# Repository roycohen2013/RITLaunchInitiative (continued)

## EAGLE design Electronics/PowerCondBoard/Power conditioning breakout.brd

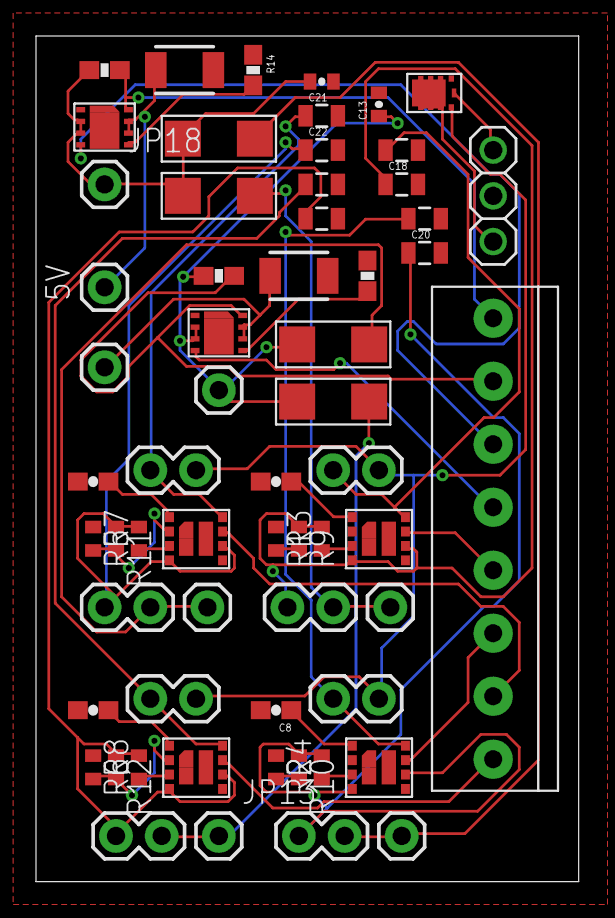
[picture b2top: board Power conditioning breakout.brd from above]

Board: 2 copper layers, 30.1 x 47.0 mm, 61 parts (0 on the bottom side), 43 nets.

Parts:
5V: M01PTH; 1X01
C3, C4: 150uF; 1210
C5, C6, C7, C8: 3.3nF; 0603-CAP
C9, C18, C19, C20, C21, C22, C23, C24: 22uF; 0805
C13, C14: .1uF; 0402-CAP
JP1: 1X08-3.5MM
JP2: 1X03
JP4, JP11, JP12, JP13, JP16, JP17, JP18: M01PTH; 1X01
JP19, JP20, JP21, JP22, JP23, JP24, JP25, JP26: M02PTH; 1X02
R1, R2, R5, R6: 180K; R0402
R3, R4, R7, R8: 10K; R0402
R9, R10: 1.02M; R0402
R11, R12: 634K; R0402
R13, R14: 20K; 0603-RES
R15, R16: 100K; 0603-RES
U$1: SI5410DU; CHIPFET
U$2, U$3, U$4, U$5: LMZ21701
U$6, U$7: TPS2556
U$8, U$9, U$10, U$11: MBRA210LT3; DO-214AC-SMA

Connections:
3.3V: C13.1, JP11.1, R15.2, U$7.P$2, U$7.P$3, U$8.P$1, U$9.P$1
+5V: C14.1, JP18.1, R16.2, U$6.P$2, U$6.P$3, U$10.P$1, U$11.P$1
EN1: JP2.3, U$1.P$6
EN31: JP1.1, U$5.P$7
EN32: JP1.2, U$4.P$7
EN51: JP1.3, U$3.P$7
EN52: JP1.4, U$2.P$7
ENT1: JP1.5, U$7.P$4
ENT2: JP1.6, U$6.P$4
F1: JP1.7, R15.1, U$7.P$8
F2: JP1.8, R16.1, U$6.P$8
GND: C3.1, C4.1, C5.2, C6.2, C7.2, C8.2, C9.2, C13.2, C14.2, C18.2, C19.2, C20.2, C21.2, C22.2, C23.2, C24.2, JP2.2, R1.1, R2.1, R5.1, R6.1, R13.1, R14.1, U$1.P$7, U$2.P$5, U$2.P$9, U$2.P$10, U$3.P$5, U$3.P$9, U$3.P$10, U$4.P$5, U$4.P$9, U$4.P$10, U$5.P$5, U$5.P$9, U$5.P$10, U$6.P$1, U$6.P$9, U$7.P$1, U$7.P$9
unnamed: C20.1, JP26.2, R4.2, R10.1, U$3.P$4, U$3.P$6
unnamed: R4.1, U$3.P$3
unnamed: R3.1, U$2.P$3
unnamed: R1.2, R9.2, U$2.P$2
unnamed: C4.2, JP4.1, U$7.P$6, U$7.P$7
unnamed: C7.1, U$2.P$1
unnamed: U$1.P$8, U$1.P$9, U$1.P$10
unnamed: R5.2, R11.2, U$4.P$2
unnamed: R2.2, R10.2, U$3.P$2
unnamed: JP12.1, JP22.2, U$9.P$2
unnamed: C8.1, U$3.P$1
unnamed: C5.1, U$4.P$1
unnamed: R7.1, U$4.P$3
unnamed: 5V.1, C3.2, U$6.P$6, U$6.P$7
unnamed: JP2.1, U$1.P$1, U$1.P$2, U$1.P$3, U$1.P$4
unnamed: R13.2, U$7.P$5
unnamed: R14.2, U$6.P$5
unnamed: C22.1, JP22.1, R7.2, R11.1, U$4.P$4, U$4.P$6
unnamed: C6.1, U$5.P$1
unnamed: C21.1, JP21.1, U$4.P$8
unnamed: C24.1, JP20.2, R8.2, R12.1, U$5.P$4, U$5.P$6
unnamed: R8.1, U$5.P$3
unnamed: R6.2, R12.2, U$5.P$2
unnamed: C23.1, JP19.1, U$5.P$8
unnamed: JP13.1, JP20.1, U$8.P$2
unnamed: JP16.1, JP24.1, U$10.P$2
unnamed: JP17.1, JP26.1, U$11.P$2
unnamed: C9.1, JP23.1, U$2.P$8
unnamed: C19.1, JP25.2, U$3.P$8
unnamed: C18.1, JP24.2, R3.2, R9.1, U$2.P$4, U$2.P$6
VIN: JP19.2, JP21.2, JP23.2, JP25.1, U$1.P$5

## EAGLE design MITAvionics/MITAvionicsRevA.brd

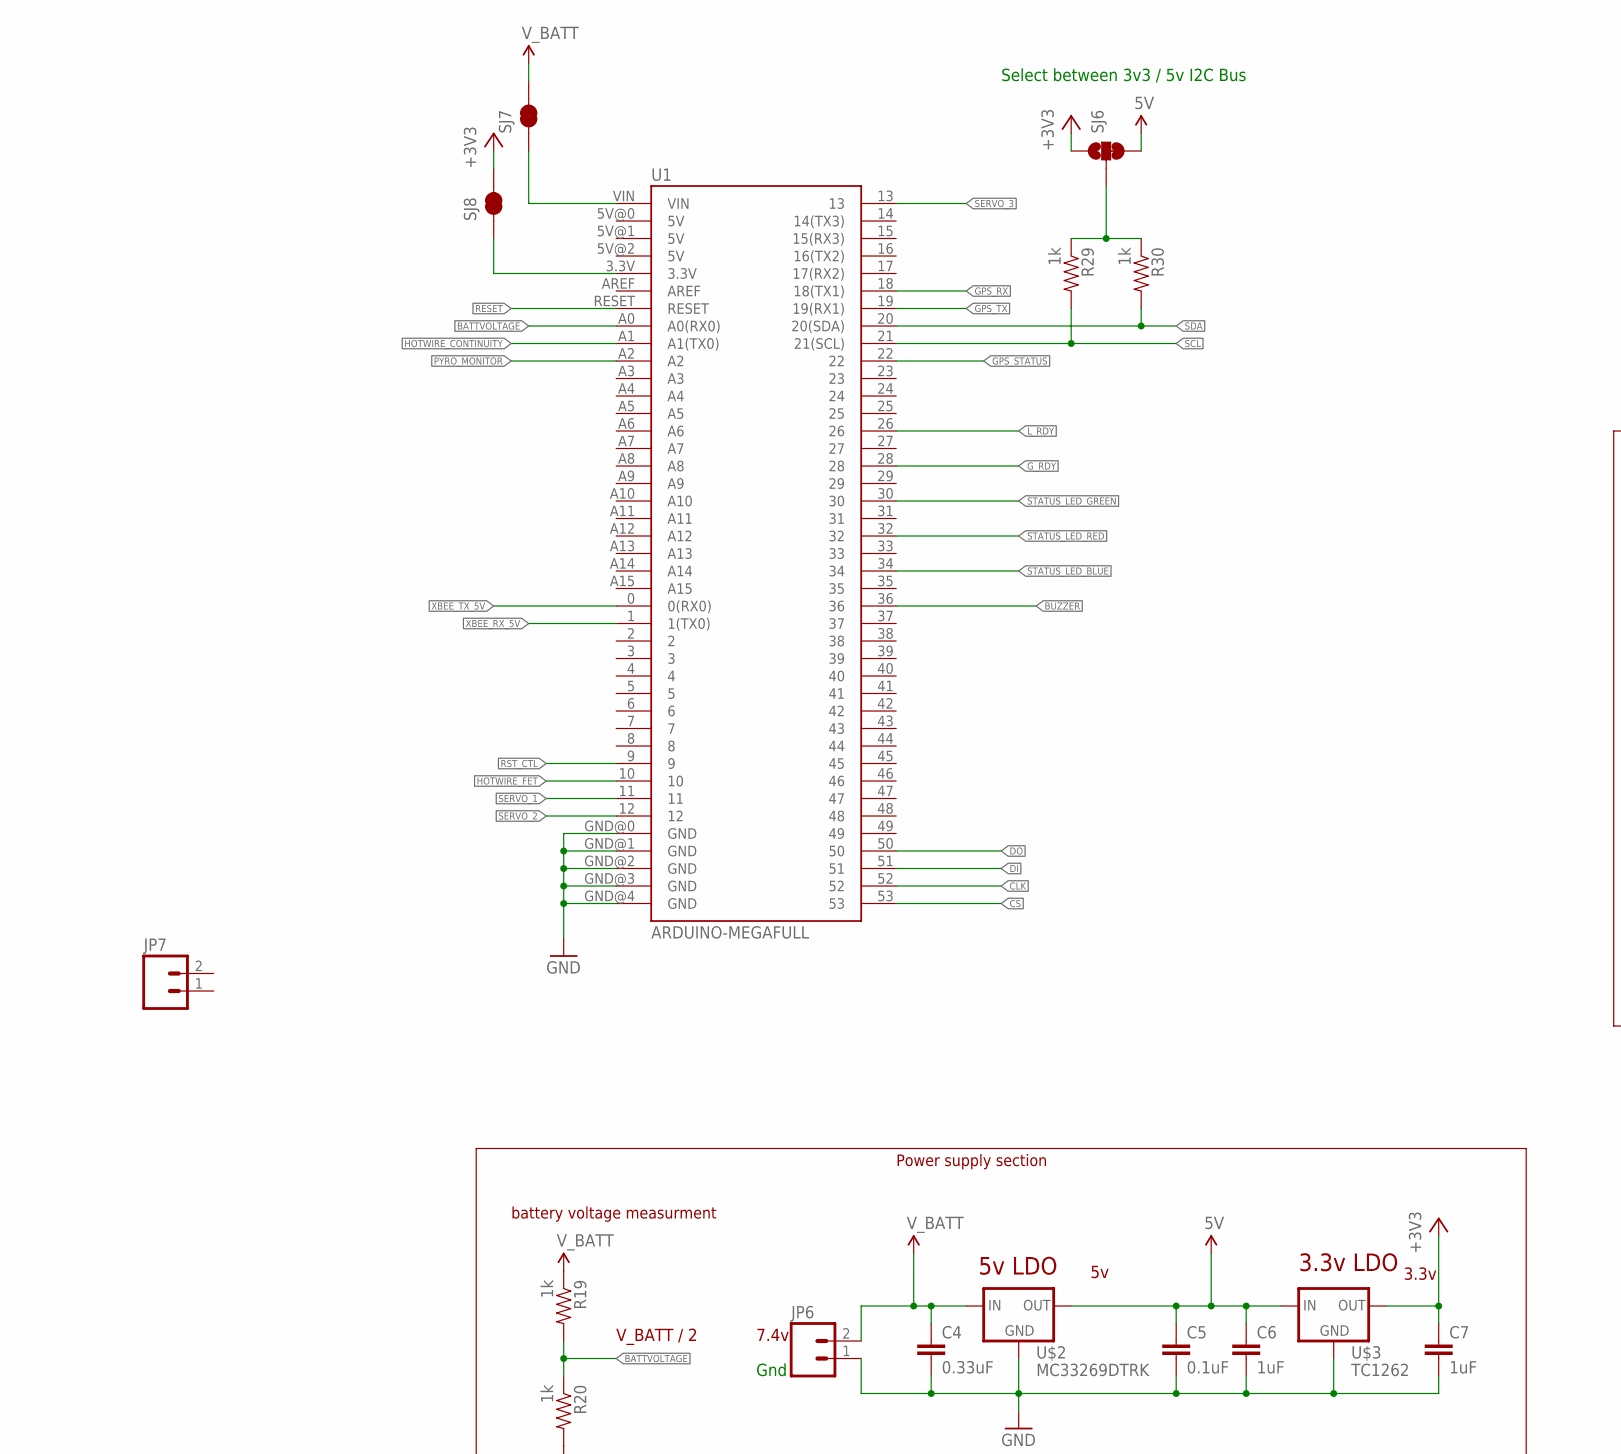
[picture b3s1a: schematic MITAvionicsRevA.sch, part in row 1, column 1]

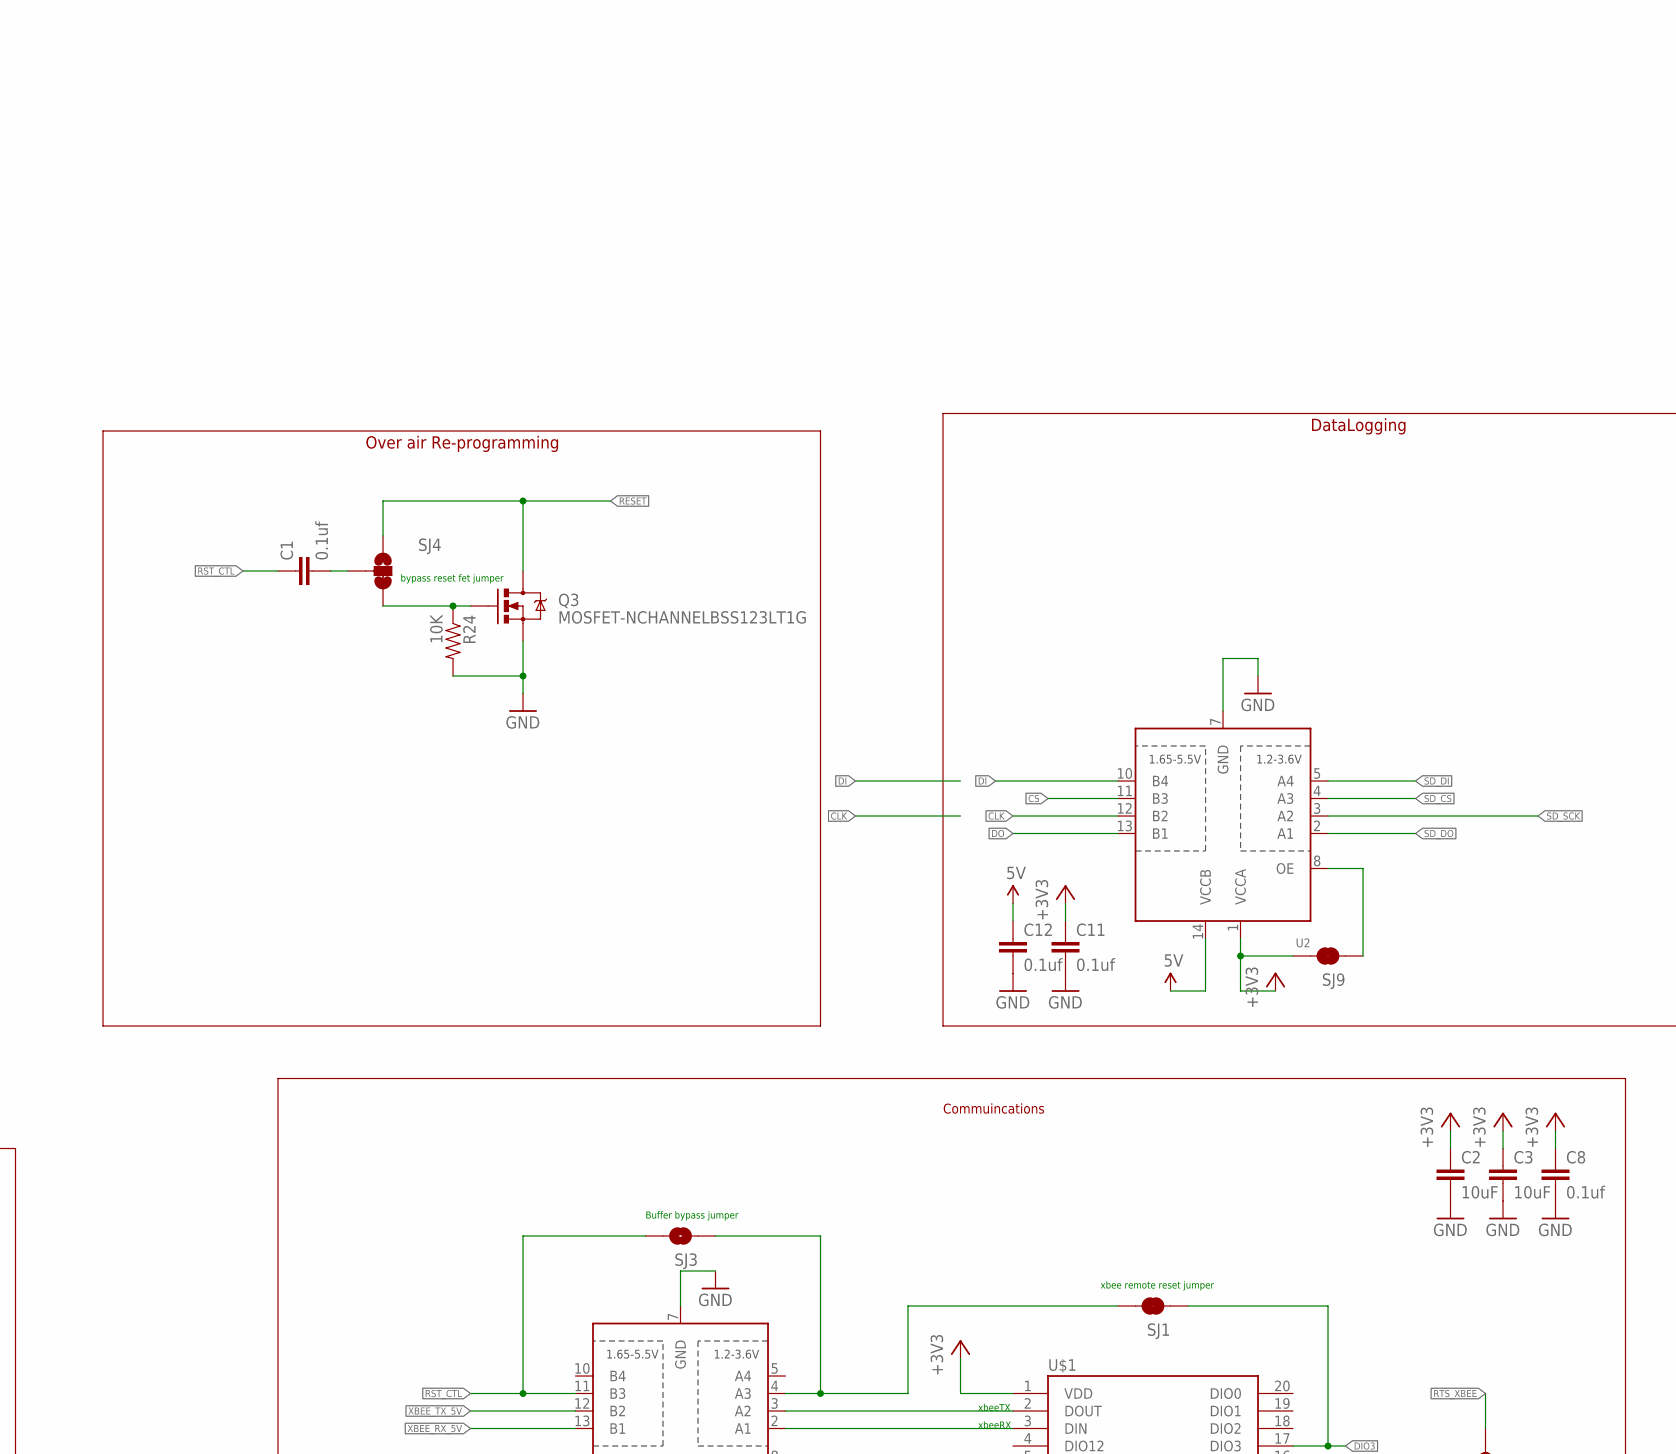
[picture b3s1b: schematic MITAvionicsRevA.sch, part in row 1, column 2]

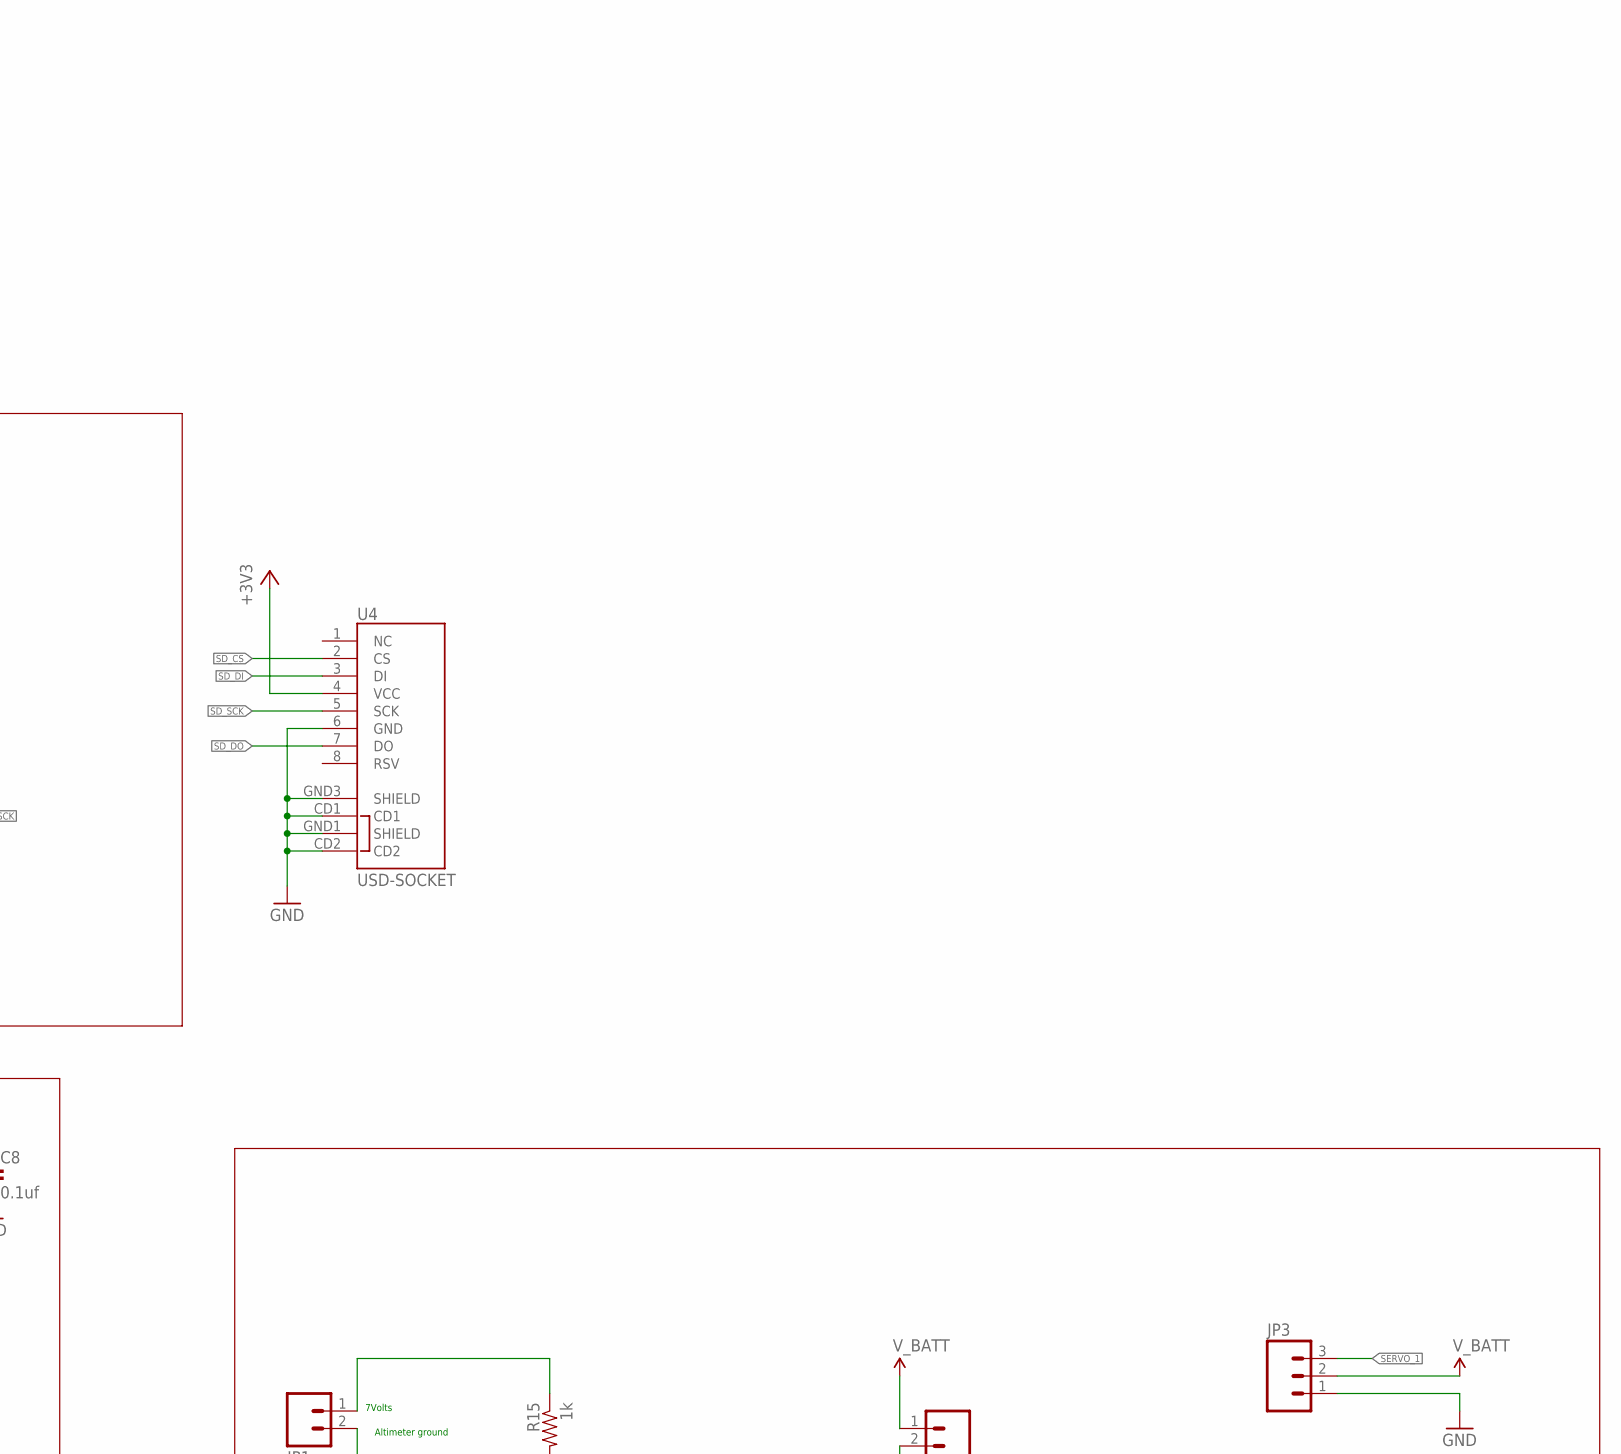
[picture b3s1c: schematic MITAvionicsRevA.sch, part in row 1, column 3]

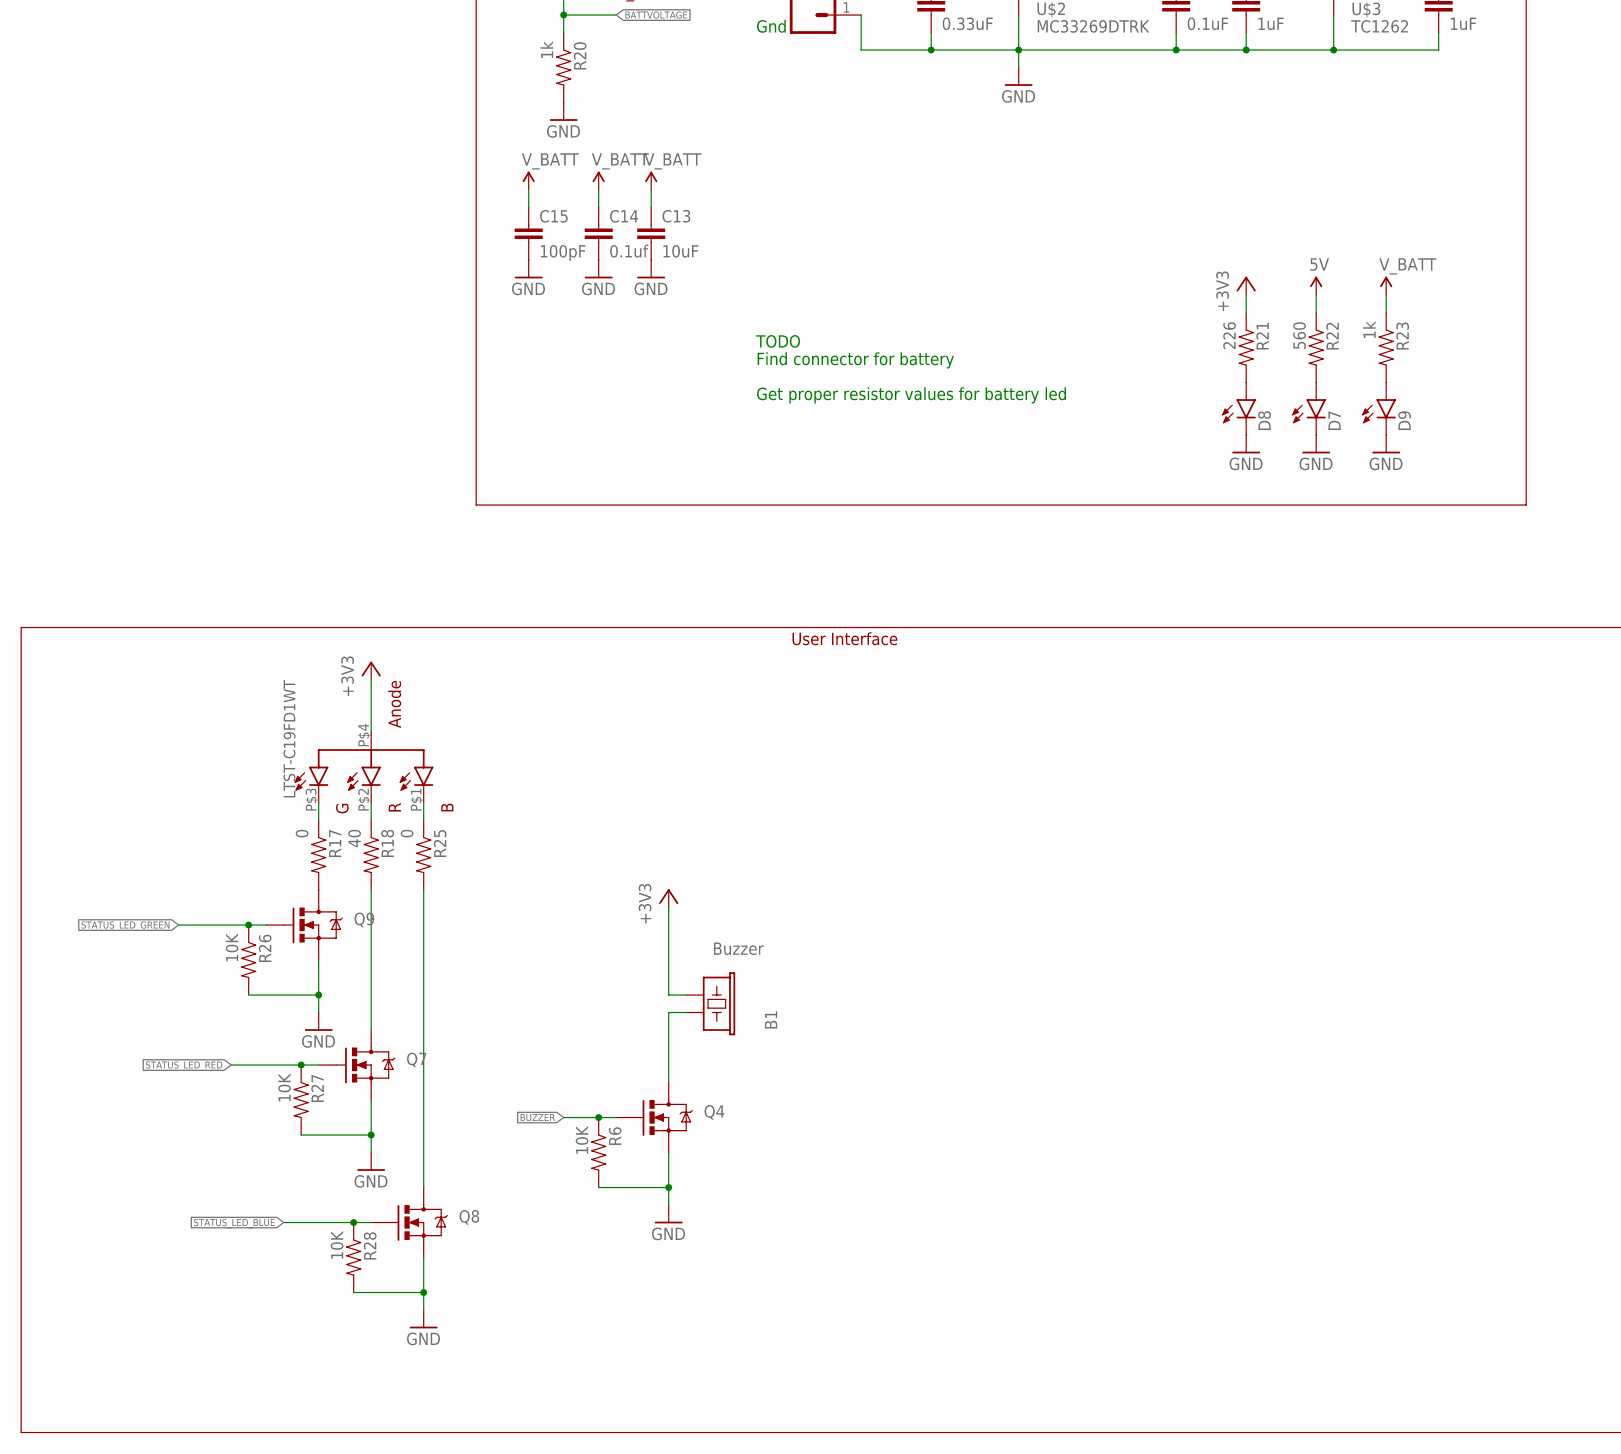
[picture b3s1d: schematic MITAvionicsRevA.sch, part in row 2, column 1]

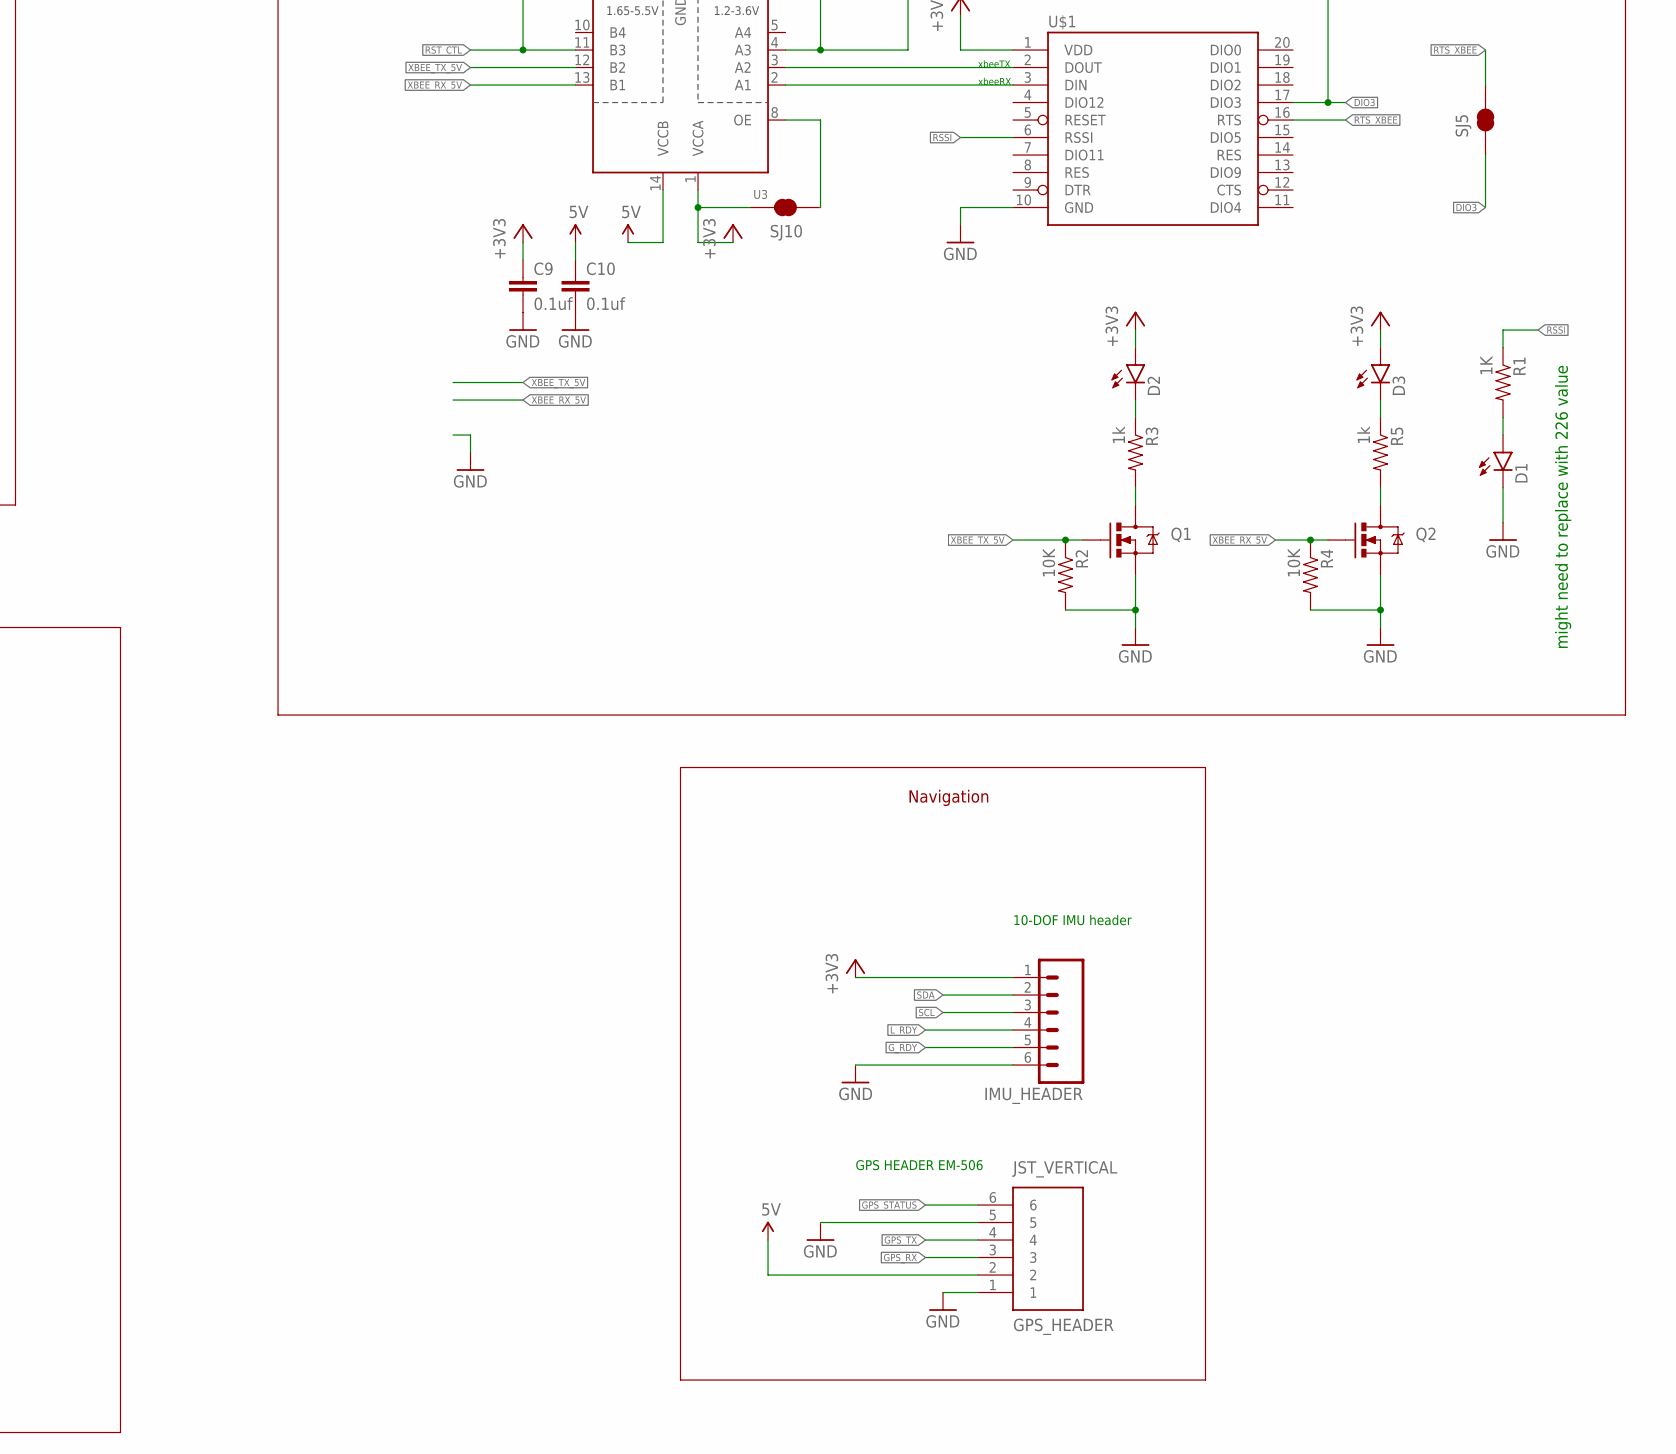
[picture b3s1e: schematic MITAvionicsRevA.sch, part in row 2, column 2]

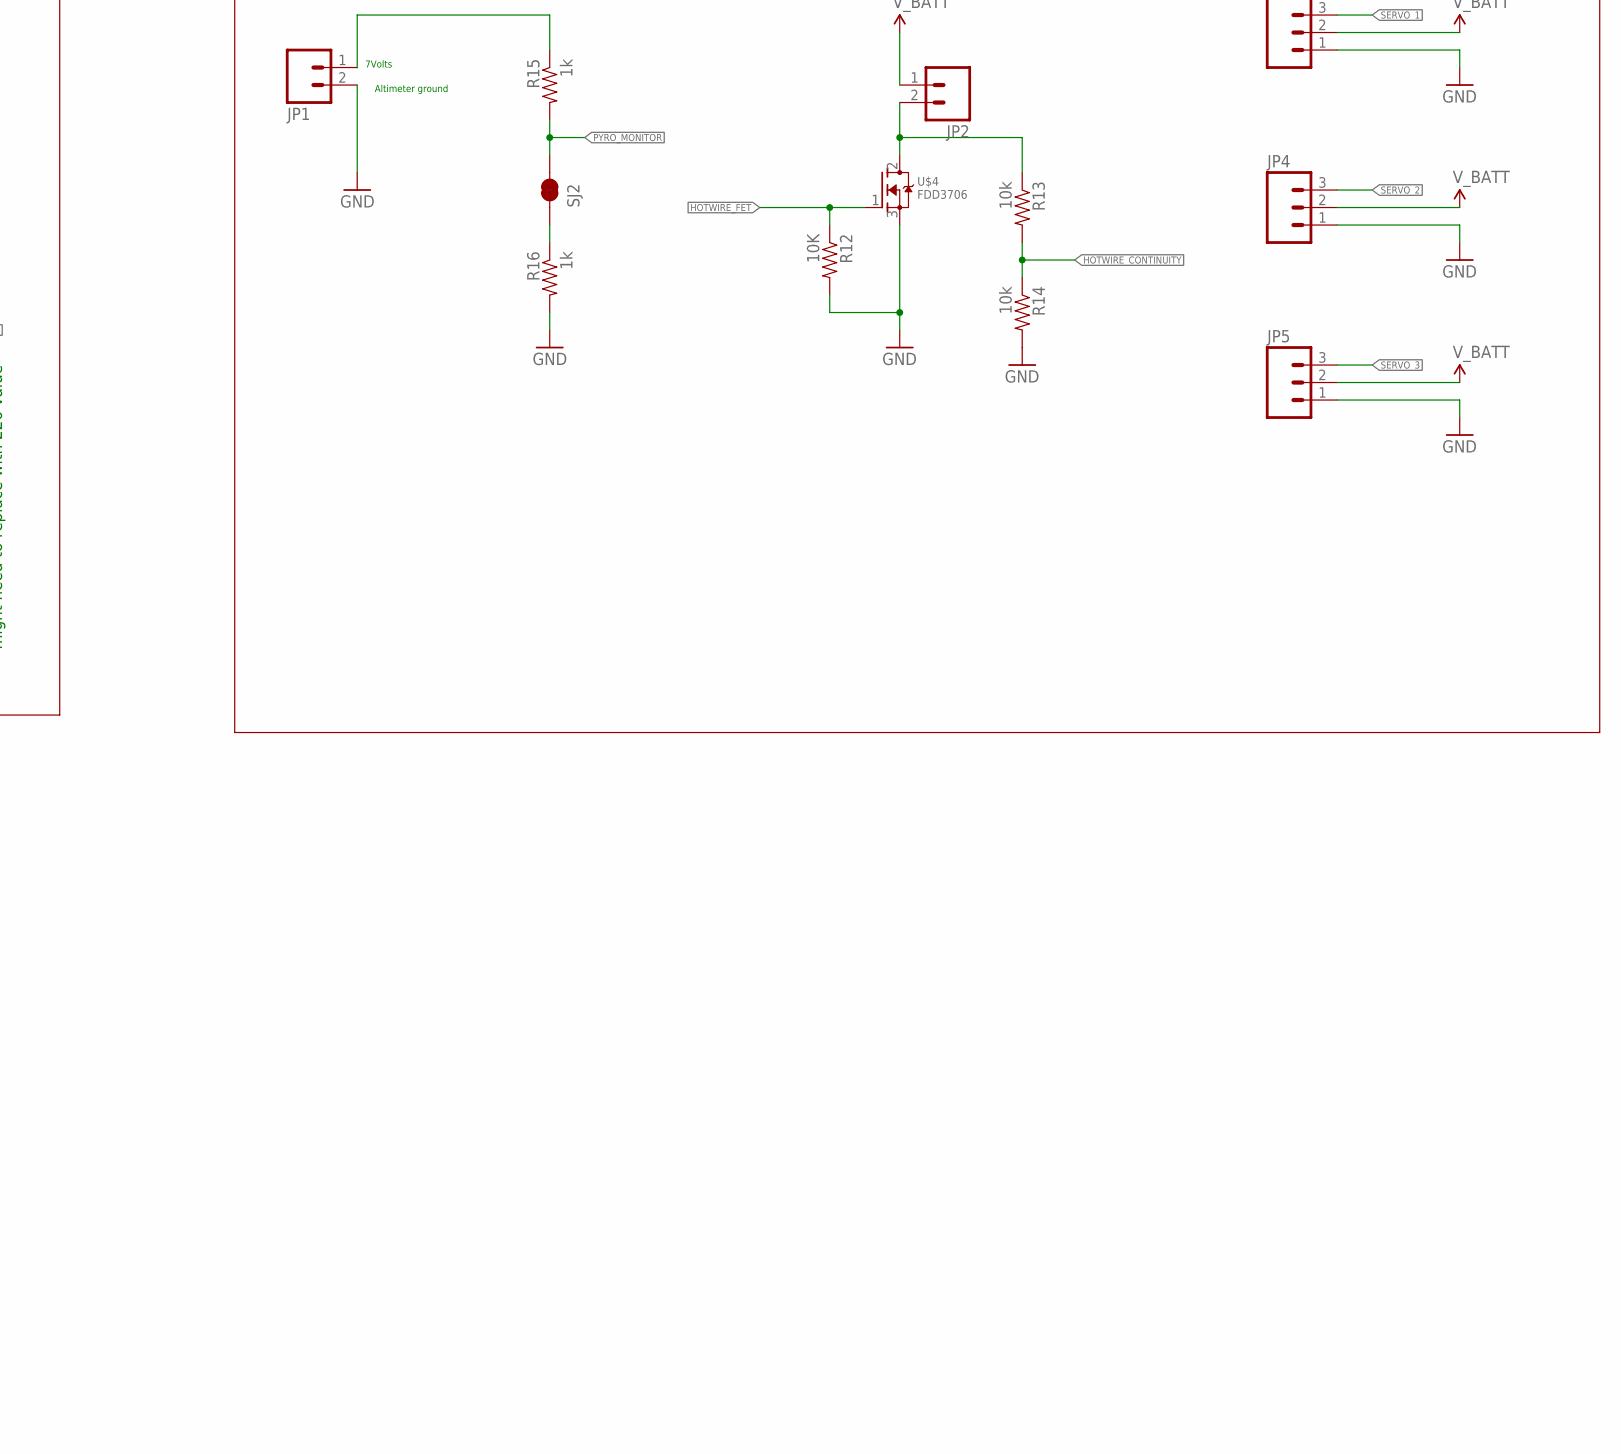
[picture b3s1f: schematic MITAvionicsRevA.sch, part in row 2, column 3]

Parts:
B1: Buzzer; BUZZER-CCV; DIGIKEY 102-1265-1-ND
C1, C8, C9, C10, C11, C12, C14: 0.1uf; 0805
C2, C3, C13: 10uF; 0805; DIGIKEY 490-3886-1-ND
C4: 0.33uF; 0805
C5: 0.1uF; 0805
C6, C7: 1uF; 0805
C15: 100pF; 0805
D1, D2, D3, D7, D8, D9: LED1206; LED-1206; DIGIKEY 160-1405-1-ND
GPS_HEADER: JST_VERTICAL; JST-6-SMD-VERT-1.0MM; DIGIKEY 455-1792-1-ND
IMU_HEADER: M06SMD-1MM; 1X06-1MM; DIGIKEY 455-1806-2-ND
JP1, JP2, JP6: M023.5MM; SCREWTERMINAL-3.5MM-2
JP3, JP4, JP5: M03PTH; 1X03
JP7: M02PTH; 1X02
Q1, Q2, Q3, Q4, Q7, Q8, Q9: MOSFET-NCHANNELBSS123LT1G; SOT23-3
R1: 1K; 0805
R2, R4, R6, R12, R24, R26, R27, R28: 10K; 0805
R3, R5, R15, R16, R19, R20, R29, R30: 1k; 0805
R13, R14: 10k; 0805
R17, R25: 0; 0805
R18: 40; 0805
R21: 226; 0805; DIGIKEY P226CCT-ND
R22: 560; 0805; DIGIKEY P560CCT-ND
R23: 1k; 0805; DIGIKEY P2.00KCCT-ND
SJ1, SJ2, SJ5, SJ7, SJ8, SJ9, SJ10: JUMPER-PAD-2-NC_BY_TRACE; PAD-JUMPER-2-NC_BY_TRACE_YES_SILK
SJ3: JUMPER-PAD-2-NOYES_SILK; PAD-JUMPER-2-NO_YES_SILK
SJ4, SJ6: JUMPER-PAD-3-2OF3_NC_BY_TRACE_SMALL; PAD-JUMPER-3-2OF3_NC_BY_TRACE_YES_SILK_FULL_BOX
U1: ARDUINO-MEGAFULL; ARDUINO_MEGA
U2, U3: TXB0104PWRSOIC14; SO14
U4: USD-SOCKET; MICROSD_1:1
U$1: XBEE-1B3; XBEE-SMD
U$2: MC33269DTRK; TO-252; DIGIKEY MC33269DTRK-5.0GOSCT-ND
U$3: TC1262; SOT223; DIGIKEY TC1262-3.3VDBCT-ND
U$4: FDD3706; TO-252
U$5: LTST-C19FD1WT; SMD-4

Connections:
5V: C5.1, C6.1, C10.1, C12.1, GPS_HEADER.2, R22.1, SJ6.3, U2.14 (VCCB), U3.14 (VCCB), U$2.2 (OUT), U$3.1 (IN)
+3V3: B1.- (2), C2.1, C3.1, C7.1, C8.1, C9.1, C11.1, D2.A, D3.A, IMU_HEADER.1, R21.1, SJ6.1, SJ8.2, SJ9.2, SJ10.2, U2.1 (VCCA), U3.1 (VCCA), U4.4 (VCC), U$1.1 (VDD), U$3.3 (OUT), U$5.P$4 (VCC)
BATTVOLTAGE: R19.2, R20.1, U1.A0 (A0(RX0))
BUZZER: Q4.1 (G), R6.1, U1.36
CLK: U1.52, U2.12 (B2)
CS: U1.53, U2.11 (B3)
DI: U1.51, U2.10 (B4)
DIO3: SJ1.1, SJ5.1, U$1.17 (DIO3)
DO: U1.50, U2.13 (B1)
GND: C2.2, C3.2, C4.2, C5.2, C6.2, C7.2, C8.2, C9.2, C10.2, C11.2, C12.2, C13.2, C14.2, C15.2, D1.C, D7.C, D8.C, D9.C, GPS_HEADER.1, GPS_HEADER.5, IMU_HEADER.6, JP1.2, JP3.1, JP4.1, JP5.1, JP6.1, Q1.2 (S), Q2.2 (S), Q3.2 (S), Q4.2 (S), Q7.2 (S), Q8.2 (S), Q9.2 (S), R2.2, R4.2, R6.2, R12.2, R14.2, R16.2, R20.2, R24.2, R26.2, R27.2, R28.2, U1.GND@0 (GND), U1.GND@1 (GND), U1.GND@2 (GND), U1.GND@3 (GND), U1.GND@4 (GND), U2.7 (GND), U3.7 (GND), U4.6 (GND), U4.CD1, U4.CD2, U4.GND1 (SHIELD), U4.GND3 (SHIELD), U$1.10 (GND), U$2.1 (GND), U$3.2 (GND), U$4.3 (S)
GPS_RX: GPS_HEADER.3, U1.18 (18(TX1))
GPS_STATUS: GPS_HEADER.6, U1.22
GPS_TX: GPS_HEADER.4, U1.19 (19(RX1))
G_RDY: IMU_HEADER.5, U1.28
HOTWIRE_CONTINUITY: R13.2, R14.1, U1.A1 (A1(TX0))
HOTWIRE_FET: R12.1, U1.10, U$4.1 (G)
L_RDY: IMU_HEADER.4, U1.26
unnamed: D1.A, R1.2
unnamed: SJ1.2, SJ3.1, U3.4 (A3)
unnamed: SJ8.1, U1.3.3V
unnamed: D3.C, R5.1
unnamed: JP2.2, R13.1, U$4.2 (D)
unnamed: Q3.1 (G), R24.1, SJ4.3
unnamed: C1.2, SJ4.2
unnamed: B1.+ (1), Q4.3 (D)
unnamed: Q2.3 (D), R5.2
unnamed: D2.C, R3.1
unnamed: Q1.3 (D), R3.2
unnamed: SJ9.1, U2.8 (OE)
unnamed: SJ10.1, U3.8 (OE)
unnamed: Q9.3 (D), R17.2
unnamed: Q7.3 (D), R18.2
unnamed: D7.A, R22.2
unnamed: D8.A, R21.2
unnamed: D9.A, R23.2
unnamed: Q8.3 (D), R25.2
unnamed: JP1.1, R15.1
unnamed: R29.1, R30.1, SJ6.2
unnamed: SJ7.1, U1.VIN
unnamed: R16.1, SJ2.1
unnamed: R17.1, U$5.P$3 (GREEN)
unnamed: R18.1, U$5.P$2 (RED)
unnamed: R25.1, U$5.P$1 (BLUE)
PYRO_MONITOR: R15.2, SJ2.2, U1.A2
RESET: Q3.3 (D), SJ4.1, U1.RESET
RSSI: R1.1, U$1.6 (RSSI)
RST_CTL: C1.1, SJ3.2, U1.9, U3.11 (B3)
RTS_XBEE: SJ5.2, U$1.16 (RTS)
SCL: IMU_HEADER.3, R29.2, U1.21 (21(SCL))
SDA: IMU_HEADER.2, R30.2, U1.20 (20(SDA))
SD_CS: U2.4 (A3), U4.2 (CS)
SD_DI: U2.5 (A4), U4.3 (DI)
SD_DO: U2.2 (A1), U4.7 (DO)
SD_SCK: U2.3 (A2), U4.5 (SCK)
SERVO_1: JP3.3, U1.11
SERVO_2: JP4.3, U1.12
SERVO_3: JP5.3, U1.13
STATUS_LED_BLUE: Q8.1 (G), R28.1, U1.34
STATUS_LED_GREEN: Q9.1 (G), R26.1, U1.30
STATUS_LED_RED: Q7.1 (G), R27.1, U1.32
V_BATT: C4.1, C13.1, C14.1, C15.1, JP2.1, JP3.2, JP4.2, JP5.2, JP6.2, R19.1, R23.1, SJ7.2, U$2.3 (IN)
XBEE_RX_3V3: U3.2 (A1), U$1.3 (DIN)
XBEE_RX_5V: Q2.1 (G), R4.1, U1.1 (1(TX0)), U3.13 (B1)
XBEE_TX_3V3: U3.3 (A2), U$1.2 (DOUT)
XBEE_TX_5V: Q1.1 (G), R2.1, U1.0 (0(RX0)), U3.12 (B2)

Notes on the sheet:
Gnd
5v LDO
3.3v LDO
battery voltage measurment
Power supply section
TODO
Find connector for battery
Get proper resistor values for battery led
xbeeTX
xbeeRX
Buffer bypass jumper
xbee remote reset jumper
bypass reset fet jumper
Commuincations
7.4v
V_BATT / 2
User Interface
7Volts
Altimeter ground
Select between 3v3 / 5v I2C Bus
10-DOF IMU header
GPS HEADER EM-506
Over air Re-programming
DataLogging
Navigation
might need to replace with 226 value

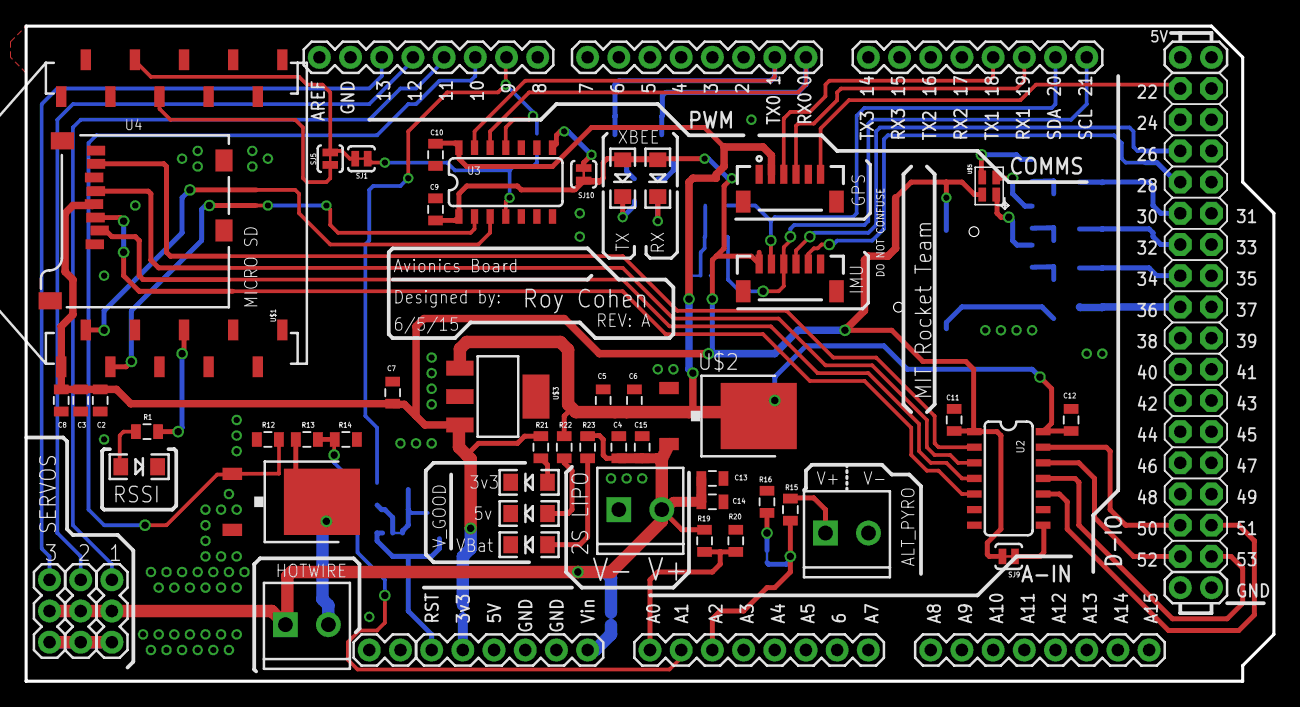
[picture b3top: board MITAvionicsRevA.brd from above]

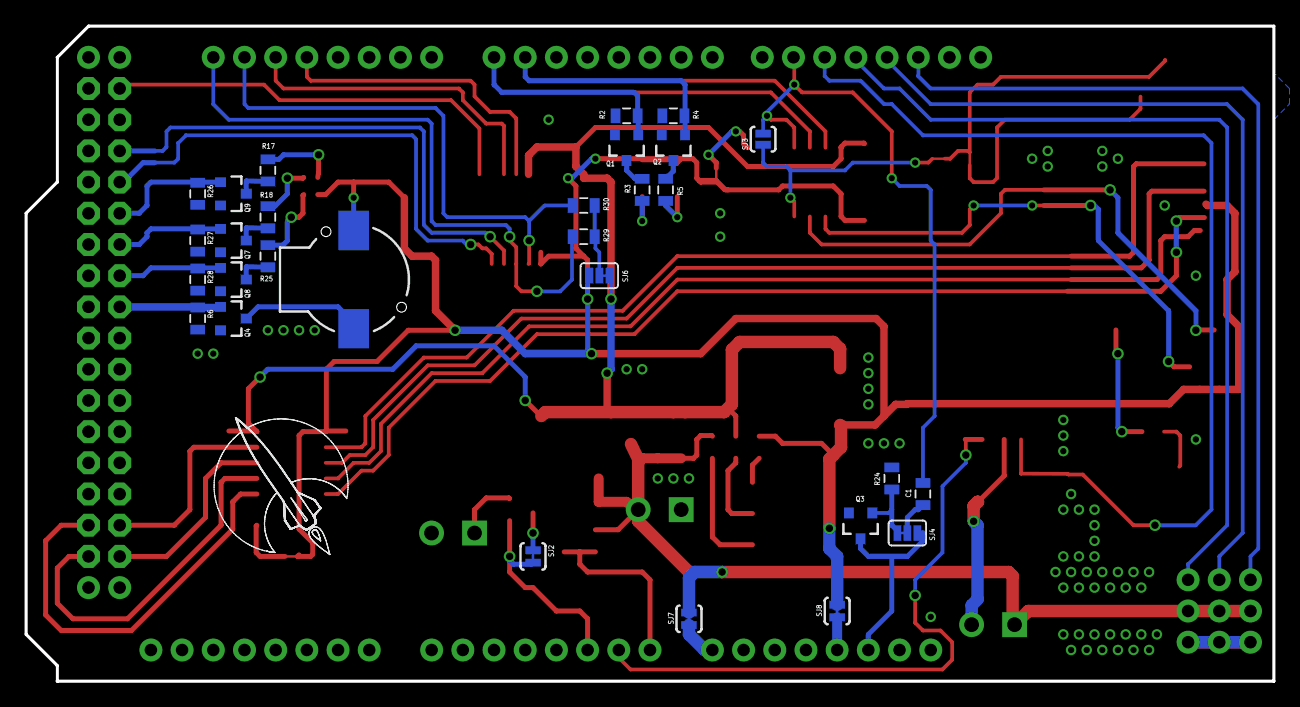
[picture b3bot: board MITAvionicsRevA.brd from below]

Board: 2 copper layers, 101.6 x 53.3 mm, 83 parts (29 on the bottom side), 65 nets.

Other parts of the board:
U$7: RITLAUNCH_LOGO_SMALLB
